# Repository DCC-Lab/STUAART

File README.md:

# STUAART

Repository of the STUAART project. 
Authors of this README : Valérie Pineau Noël, Nathan Bérubé and Daniel C. Côté (DCC/M-lab, CERVO brain research center, Université Laval)

## Overview

STUAART is an automated weighing system for mice that tracks individual weights over weeks. Each cage holds three independent scales ; each scale is a load cell (Wheatstone bridge) read by an HX711 24-bit amplifier connected via a 2-pin protocol (DOUT, SCK) to a DFRobot FireBeetle ESP32 V1 microcontroller. The microcontroller logs every measurement to a microSD card and exposes a small HTTP server so a host can pull today's CSV over Wi-Fi.

## Repository layout

| Folder | What's there |
|---|---|
| `Arduino/` | Custom libraries and scripts to run the STUAART. |
| `KiCAD/` | PCB schematic and design mde on KiCAD (version 10.0.7). |
| `CAD/` | Mechanical 3D files for the scale platforms. Print the top platform with high infill density to keep stiffness and reduce creep. |
| `FlaskServer/` | Python script used to catch the data and save on a local NAS. |
| `Notebooks/` | Notebooks that users can run in Google Colaboratory for data post-processing. |

## Getting started with the firmware

1. Install Arduino IDE 2.x or `arduino-cli`.
2. Add the Espressif boards URL in Preferences and install the `esp32` core (board package). 
3. Copy and save files in folder `Arduino` on your computer. 
4. Copy and save the Python script in `FlaskServer` in your local NAS and run it. 
5. If you are using a new Firebeetle ESP-32 board, run `Arduino/FormatSPIFFS/FormatSPIFFS.ino` (prevent error `SPIFFS Mount Failed`). Otherwise, go to the next step. 
6. Open `Arduino/STUAART/STUAART.ino`.
7. Download third-party libraries in the Arduino IDE. See section *Required third-party libraries*.
8. In the Arduino IDE, pick board `FireBeetle-ESP32` (`esp32:esp32:firebeetle32`) in  Tools -> Port, pick the USB serial port, then Verify and Upload.

## Required third-party libraries

Install these via Arduino IDE Library Manager (Sketch -> Include Library -> Manage Libraries):

| Library | Author | Tested version |
|---|---|---|
| HX711 | Bogdan Necula (bogde) | 0.7.5 |
| RTClib | Adafruit | 2.1.4 |
| ArduinoJson | Benoit Blanchon | 7.0.4 |

## A minimal load cell read

```cpp
#include "LoadCell.h"
#include "LoadCellController.h"

LoadCell loadcell;
LoadCellController controller;

void setup() {
  Serial.begin(115200);
  controller.add_loadcell(loadcell);
  controller.easy_start_with_params(
      1,        // loadcell number
      27,       // DOUT pin (avoid GPIO 6-11, those are the flash bus)
      17,       // SCK pin
      true,     // calibrate offset
      true,     // calibrate scale
      false,    // read offset from memory
      false,    // read scale from memory
      true,     // save offset to memory
      true,     // save scale to memory
      0,        // manual tare offset (0 = not specified)
      0,        // manual scale coeff (0 = not specified)
      128       // gain, do not change
  );
}

void loop() {
  controller.wait_ready_timeout(1, 1000);
  float reading = controller.get_weight(1);
  Serial.println(reading);
}
```

## Manual calibration mode VS Automatic mode

STUAART has a switch that dictates the mode at reboot. Manual calibration mode is used to save new persistent parameters (tare offset and scale coefficients) in the SPIFFS. These parameters are used to convert digital signals received from the HX711 amplifier to mass values in grams. For this step, objects of known mass must be used. The users can use as many objects of known mass as they want for calibration. Automatic mode is used when the users want to use the parameters previously saved in the SPIFFS. The authors suggest to start with the manual calibration mode when starting a new experiment. Connecting the STUAART to a computer will allow the users to make sure that everything is working well and save new calibration parameters. Then, for continuous, longitudinal measurements, the automatic mode can be turned on and the system can be powered via a standard wall adaptor. 

## Mass time series analysis

Each step of the post-processing analysis can be performed using notebooks run via Google Colaboratory. To begin, the raw mass time series must be uploaded to the user's personal Google Drive. We also recommend that users save a personal copy of each notebook to their own Google Drive by clicking on *File > Save a copy in Drive* once opened via the links below. Users are free to modify their own versions of the notebooks as desired. 

1. **Remove buffer flush indicators from the raw mass time series** : String such as "--, --, --, -- \n" are saved in the raw data to indicate the moments when the buffer flushed its contents onto the SD card. This data can be used to evaluate the time it takes to flush all data and how many times the buffer flushes the data over a given period. For further analysis, these indicators nust be removed. You can do this using this notebook :

2. **Correct for baseline shift and remove outliers** : This step is the most computationally intensive. Longitudinal mass time series are affected by mechanical and thermal drifts that alter the value of the initial tare and shift the measured mass by multiple grams, which must be corrected to ensure accuracte evaluation. Additionally, transient spikes can occur and should be filtered out. Users can choose whether to remove outliers and select which baseline correction algorithm best suits their data. Four baseline correction algorithms are provided : density-based spatial clustering of applications with noise (DBSCAN), kernel-density estimation (KDE), Gaussian mixture model (GMM) and a custom rolling-mean filtering. As presented in the main manuscript, the authors achieved optimal results with DBSCAN, while the custom rolling-mean filtering performs well for more stable data sets. We also provide a graphical user interface (GUI) for manual baseline fine-tuning and quick data visualization. We suggest testing different algorithms and using the notebook *Compute_metrics.ipnyb* to evaluate quantitatively the accuracy and precision of the baseline-corrected mass compared to ground-truth mass measurements. If ground-truth data was not acquired, a simple visual inspection of the baseline-corrected mass time series can guide algorithm selection. More information is available in the supplementary information document and within the notebook :

3. **Display mass time series and compute mass per time bin** : After baseline correction and outlier removal, the users can display the mass time series for visual evaluation. The data can be displayed per scale, for the overall measured mass of the system (summed mass time series per timepoint) and by the relative mass change (where the mass at time = 0 hour is 0%). The users can also obtain the mass per time bin. 

4. **Compute metrics** : Quantitative evaluation of the mass compared to ground-truth measurements can be obtained via this notebook : 

5. **Evaluate location, grid-hanging and active state behaviors** : Three additional notebooks are provided to identify and evaluate the spatial occupancy of each scale, the grid-hanging behavior and the active VS inactive states over time. 
   - Location : 
   - Hanging : 
   - Activity : 

## Error management 

- `Unable to verify flash chip connection` : the default upload speed of 921600 baud is too fast for the CH340 USB-serial chip on the FireBeetle. Set 115200. 

- `SPIFFS Mount Failed` : Run the script in `Arduino/FormatSPIFFS/FormatSPIFFS.ino`. 

- The "GPIO 9 = flash" issue on cell 1 is the root cause of corrupted readings (raw == 0xFFFFFF returned as -160.68 g). A defensive software patch in `LoadCell.cpp` rejects this signature, but the long-term fix is to reroute that DOUT to GPIO 25 or 26 (silkscreen D2 or D3).

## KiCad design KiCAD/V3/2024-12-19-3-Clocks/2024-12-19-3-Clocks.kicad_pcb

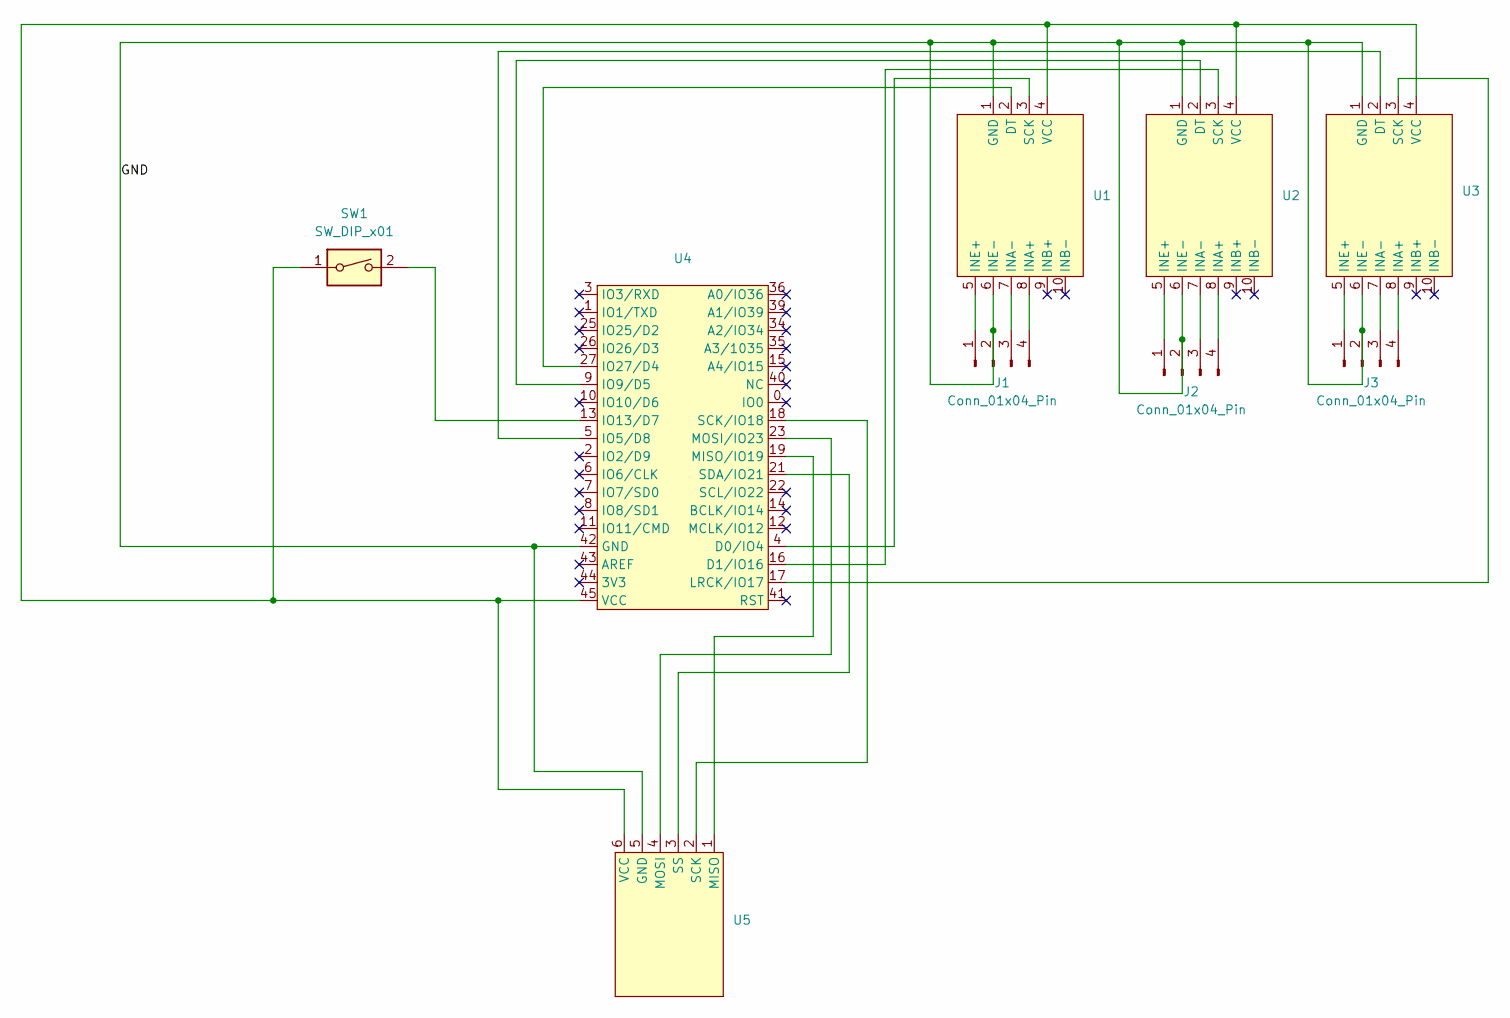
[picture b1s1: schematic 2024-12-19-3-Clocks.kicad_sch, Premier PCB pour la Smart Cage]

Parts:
J1, J2, J3: Conn_01x04_Pin; JST_PH_B4B-PH-K_1x04_P2.00mm_Vertical
SW1: SW_DIP_x01; SWITCH SLIDE DIP SPST 25MA 24V
U1, U2, U3: HX711
U4: Firebeetle ESP32
U5: MicroSD DFRobot

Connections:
/GND: J1.2, J2.2, J3.2, U1.1 (GND), U1.6 (INE-), U2.1 (GND), U2.6 (INE-), U3.1 (GND), U3.6 (INE-), U4.42 (GND), U5.5 (GND)
unnamed: J1.1, U1.5 (INE+)
unnamed: J1.3, U1.7 (INA-)
unnamed: J1.4, U1.8 (INA+)
unnamed: J2.1, U2.5 (INE+)
unnamed: J2.3, U2.7 (INA-)
unnamed: J2.4, U2.8 (INA+)
unnamed: J3.1, U3.5 (INE+)
unnamed: J3.3, U3.7 (INA-)
unnamed: J3.4, U3.8 (INA+)
unnamed: U1.2 (DT), U4.27 (IO27/D4)
unnamed: U1.3 (SCK), U4.4 (D0/IO4)
unnamed: SW1.1, U1.4 (VCC), U2.4 (VCC), U3.4 (VCC), U4.45 (VCC), U5.6 (VCC)
unnamed: U2.2 (DT), U4.9 (IO9/D5)
unnamed: U2.3 (SCK), U4.16 (D1/IO16)
unnamed: U3.2 (DT), U4.5 (IO5/D8)
unnamed: U3.3 (SCK), U4.17 (LRCK/IO17)
unnamed: SW1.2, U4.13 (IO13/D7)
unnamed: U4.19 (MISO/IO19), U5.1 (MISO)
unnamed: U4.23 (MOSI/IO23), U5.4 (MOSI)
unnamed: U4.18 (SCK/IO18), U5.2 (SCK)
unnamed: U4.21 (SDA/IO21), U5.3 (SS)

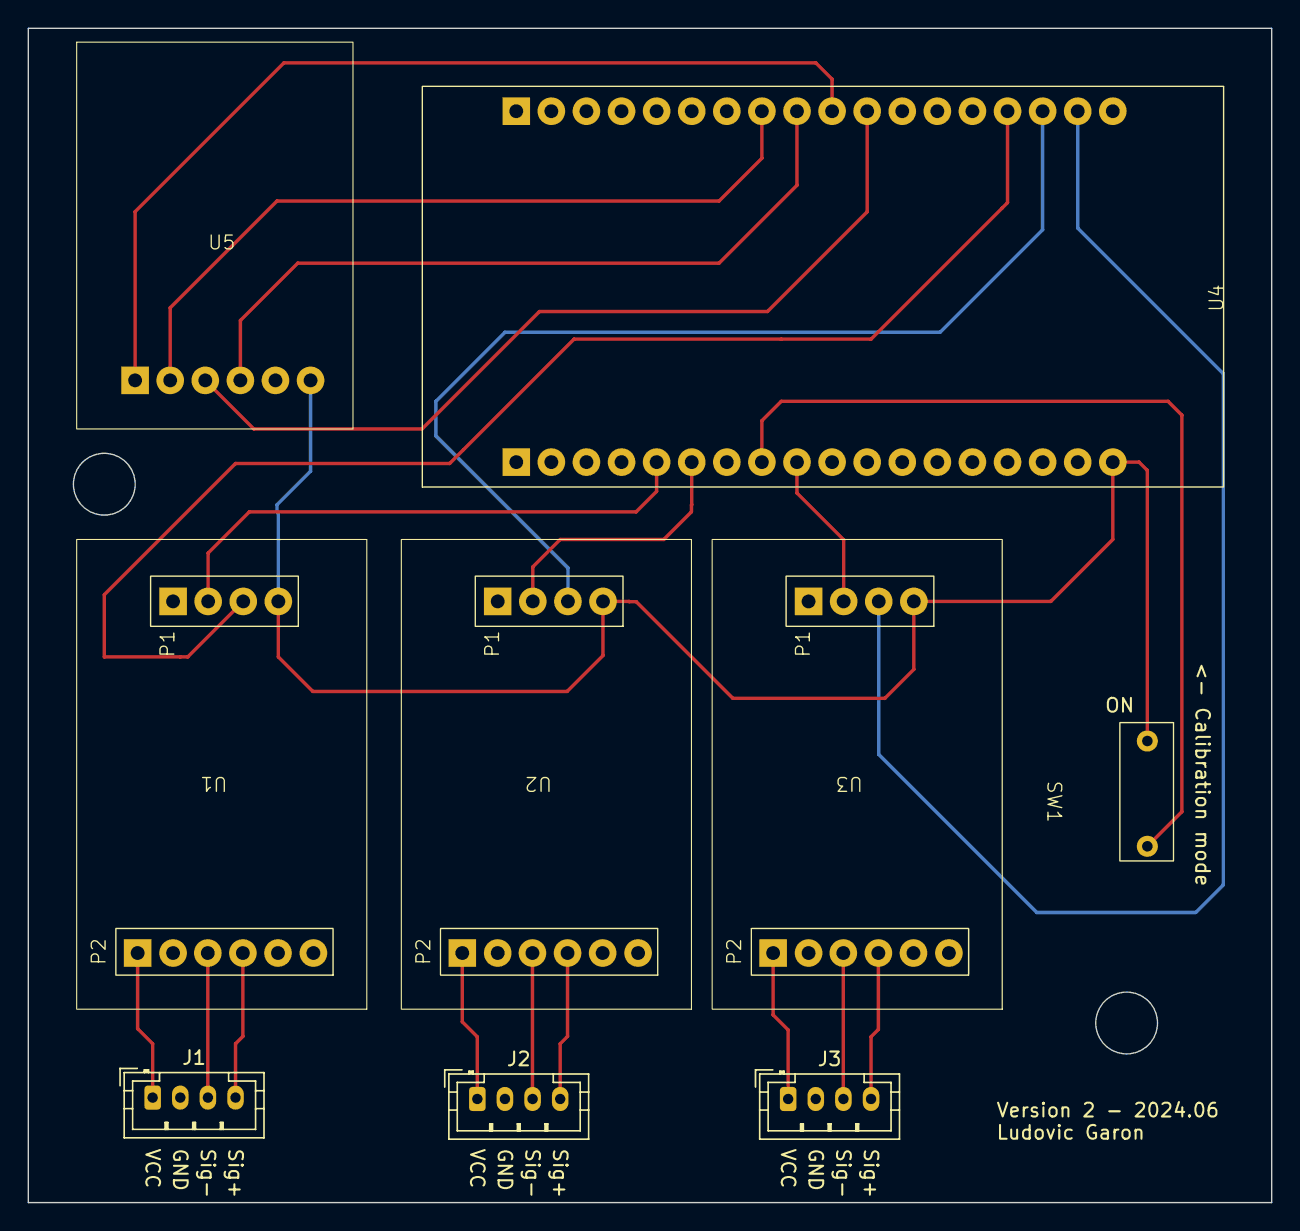
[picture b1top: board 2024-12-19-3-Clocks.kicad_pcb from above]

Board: 2 copper layers, 90.0 x 85.0 mm, 9 parts (0 on the bottom side), 22 nets.

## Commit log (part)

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2023-07-13 Add drift data and drift arduino code
    Add drift data and drift arduino code used in all drift tests
2023-07-17 Change in files organisation
2023-07-18 Loadcell and Loadcell_controller librarieslibraries
    First commit of the two Arduino libraries
2023-07-19 Applying F() macro on strings/syntax corrections
    To avoid stocking strings in variables memory, the F() can be used to save on sketch memory. The variables was full without this step when compiling.
2023-07-19 Description of Loadcell_controller methods/make methods protected
    Easy_ methods were put in protected since they are only called in easy_start_with_params() and calling them somewhere else wouldn't be adapted.
2023-08-16 Add doxygen documentation and comment
    The two libraries were documented with doxygen formated docstrings. A few functions were added to LoadCellController class to access a LoadCell completely through the LoadCellController
2023-08-16 Add link to github for libraries in headings
2023-08-18 Modification CAD .stl files
2023-08-20 change in folde name
2023-08-20 File name change
2023-08-21 Add capacitive sensor sketch example
2023-08-22 Change directory name
2023-09-26 Update README.md with an easy start code for one loadcell
2023-10-11 LoadCellController compiles for EEPROM and SPIFFS
    The read/save_from_peristent_memory now support both EEPROM and SPIFFS. The code detects wich chip is connected and the behaviour of the member functions are adapted to the type of memory. Not tested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
2023-11-01 SPIFFS fully working
    The library is now adapted to support both EEPROM and SPIFFS. The documentation was adapted to this new version.
2023-11-02 Sketch to format SPIFFS
    Creation of a sketch to format SPIFFS on a FireBeetle when used for the first time
2023-11-10 Update WeightReadingWithRecalibrationModeSwitching.ino
    Remove useless Serial.print()
2023-11-24 Add sketch examples
    Modify the mode switching sketch to make it work with SD card. Adding a file with functions which can manage the file on the SD card and read them.
2023-12-10 Linear test
    Adding the data, python code for graph and the firebeetle sketch for the linearity test of a 100g load cell.
2023-12-20 Test of a 300g load cell with 200g
    Arduino sketch for the experiment, the csv data file and the python code to produce a simple graph.
2024-01-12 Create TestLoadCellandHX711.ino
    Creation of a simple script to verify if all components are working
2024-01-12 Create LoadCellCircuit.png
    Scheme of the circuit for a load cell
2024-02-07 Correct number of readings averaged bug
    The read_average() from HX711 library was used instead of read_raw_average(). No number of averaged readings was specified in input because my custom library always uses the class variable. But, read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
2024-02-14 Recalibration of offset with absolute value on measurement
    The condition of recalibration if the offset in get_weight_with_auto_recalibration() is a threshold. The comparison between the measurement and the threshold wasn't unsigned. The absolute value is no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
2024-02-14 Create 20240214_outliersfiltering.py
    First version of outliers filtering on weight data with python
2024-03-20 Add new raw weight data with mouse (2024.02.14)
2024-03-20 Add super().__init__ in Data class
    make sure that the Data object will have all the attributes of np.ndarray type
2024-03-27 Add all visualization functions and simple filtering
2024-04-03 Baseline fitting version 1
    First version of the baseline fitting functions.
2024-04-10 Référer à mon .md pour les petits changements que j'ai faits
2024-04-16 2024.04.15 : Ajout d'un seuil pour les outliers négatifs qui est différent du seuil pour les outliers positifs
2024-04-17 Update and add docstring shift_data_to_zero function
    I changed the name center_data_on_zero to shift_data_on_zero to make it clear that the data is only shifted to zero and not around its mean
2024-04-17 Complete documentation of functions in Data class
2024-04-17 Add documentation and correct a few mistakes
2024-05-07 creating 2 main.py version
    mainv2.py uses the Cage class
2024-05-07 add fft filtering
2024-05-07 add automatic initial offset calculation
    first offset is now calculated from the first stable values. average is taken. the code can find how many values to average based on a tolerance on stability
2024-05-07 update mainv1.py for tests
    commenting and uncommenting sections to see signal at different steps in processing
2024-05-21 Adding convolution filtering
2024-05-21 add comments in mainv2
2024-05-28 indent fix
2024-05-28 Added files based on 2023-11-27 code
2024-05-29 Added creation of test files and changed wifi name/password
2024-05-29 Moved file to fit arduino, Changed way we send data
2024-05-30 Put every functions before arduino setup and loop
2024-05-30 Started documentation, put the saved files in a folder in user documents
2024-05-30 Added doc to python methods
2024-05-30 Added functions documentation in the arduino code
2024-05-30 added log folder to keep things clean
2024-05-30 Smooth mean weight change over time and correct for boundary effects from convolution
    - convolution_filter() is now convolution)filter_with_egde_padding(). The boundary effect from the convolution filtering is corrected with edge padding.
    - added the function "reset_data()" to reset the data to the raw data after a certain task is completed.
    - the function compute_mean_data() produces a smooth weight change over time. The level of smoothness can be adapted with the variable smooth_level.
    -
2024-05-31 added mechanism to create a file everyday to which we should concatenate.
    Added a small part of code to make it minutes rather than days because otherwise it would be too long to test easily.
2024-05-31 Added first delayed fetch of the data
2024-05-31 Standardized the naming conventions
2024-05-31 Added a function to generate a number of ips from the first one and the number of ips that you want
2024-06-03 renamed and now using non-deprecated accessors
2024-06-03 Add Cage Sketch to measure weight (used on 20240407)
2024-06-03 fixed function description to fit actual function
2024-06-03 Copied files from 20240530 to continue
2024-06-04 Fixed writing to files so we create rows with each data
2024-06-04 Moved folders to make it more manageable and to keep traceability.
    We should always modify the same file rather than creating new ones for every test.
2024-06-05 reindented code
2024-06-05 commented out code and made it save every day
2024-06-06 Total hanging is done
    I made the total hanging time accuracy and the hanging identification accuracy. I changed the way we remove outliers, I added a function in CageClass to identify when the mouse gets in the cage at th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
2024-06-06 added security to make sure we don't save today's data in tomorrow's file. Shouldn't happen, but better be safe than sorry
2024-06-06 added reconnection to wifi after an hour to make sure the device stays connected. Commented out most of the serial prints to get faster acquisition
2024-06-07 server accepts a custom file specified to be sent
2024-06-07 added test file and buffering data
2024-06-07 accelerated data transfer over wifi
2024-06-07 made delays between failed attempts to download an hour rather than 30 seconds to give the Firebeetle time to reconnect.
2024-06-10 added function comments on saving to server
2024-06-10 testing thread timer
2024-06-10 removed test csv
2024-06-11 changed from 6 hours loops to 12 hours
2024-06-13 Hanging moments are identified with a total time accuracy of 88.6% and a hanging identification accuracy of 90.9%
    Hanging is identified by :
    - removing outliers, aka removing measurements that are alone and very different from its neighbours.
    - convoluting with a small window (15 points) and doing the mean, so passing a square function
    - using the function compute_hanging(), which identifies the total hanging time, the moment of hanging and the hanging frequency.
    I compare my results with the real moments of hanging that I identified manually from the video.
2024-06-13 Hanging events are identified correctly
    1. Remove outliers (outliers = points that are very different from their neighbours)
    2. Convolve with a small window (15 points) to smoothen the data
    3. High-pass filter in convolution. Identifies moments when the weight data changes drastically.
    4. I use conditions to verify where are the hanging events according to the number of points between the start index and the end index. For example, if the number of points between start and end is u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
2024-06-13 Done
2024-06-22 Small corrections + test new measurements from pcb version 2
2024-06-27 put the saving interval to 0
2024-06-27 creating folders on remote server recursively
2024-07-02 modified comment to make it clearer
2024-07-02 Added calendar ui with button sending the file we want to fetch
2024-07-04 added build files to gitignore
2024-07-04 added method documentation
2024-09-03 Paste last script for overnight mouse recording
2024-09-03 Added kicad files for pcb v2
2024-09-18 Update CageClass.py
    je regarde maintenant tous les pics ensemble, sans discriminer les négatifs et les positifs, suite à un filtre passe-haut sur les séries temporelles de poids et je regarde tous les intervalles si la 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
    Ça fonctionne super bien SEULEMENT quand la souris est sur une balance à la fois
2024-09-26 Compute number of entries per scale
    compute_location_on_scale() will now compute the number of entries per scale.
2024-10-10 Location is identified and evaluated compared to ground truth from video
    The location of the mouse is identified correctly with the weight data from individual time series of each scale. The total error and precision is computed as well with a different class method.
2024-12-04 Added forced fast clock and SD card library
2024-12-18 Moved load cell library files inside arduino folder so when we modify the code it automatically modifies what is used
2024-12-18 added option to enable or disable save to SD Card taring of loadcells
2024-12-18 testing saving data with 3 loadcells
2024-12-18 PCA of dataset of 2 seconds per behaviour event is done and cluster somehow good the different data, but mostly the different scales
2024-12-19 This setup doesnt give outliers
2024-12-19 FFT of weight data
    FFT of weight data per type of behaviour is performed. There is no specific frequency that is present in the grooming that that can differentiate it from the other types of behaviour.
2024-12-19 Using different clock pins for the load cells
2024-12-19 Updated README.md, added small tutorial on how to use the branch
2025-02-17 Je ne sais pas
2025-03-31 Create Test2LoadCellandHX771.ino
    Sketch example to use two loadcells using two different sck pins and only reading raw data.
2025-03-31 Update Test2LoadCellandHX771.ino
    change description in the sketch
2025-05-28 IMproved the README for completeness
    Added more context
    Added table of content
    Added info on exact versions of libraries to install
    Added info on where to find the library directory
2025-05-28 Update FireBeetleServer.ino
    IMproved use of logf() through out the main code.
2025-06-03 Many changes, mostly cosmetics, but some imnportant
    * The LoadCell and LoadCellController are now in the main directory of the ino file.
    They do not need to be in the librairies folder, and this makes verything simpler
    since they remain in the Git context.
    * Now using the ArduinoLog libraries for a clean, controllable log with log_levels.
    * Reformatted everything
2025-06-04 IMproved time kleeping: fall back on time since boot if date is not available.
    Also, use string instead of char*;
2025-10-01 Remove comment in 20250924-SketchExampleOneScaleSDCardSwitchWifi.ino
2025-10-01 Add network and password information to 20250924-SketchExampleOneScaleSDCardSwitchWifi.ino
2025-10-27 Change threshold to find peaks from 15 to 10 to identify correctly hanging events
2025-11-03 Print baseline data and its FFT of the system and of the 3 scales separately
2025-11-04 PCA and ICA on power spectra, then HDBSCAN
    Both don't really work, but PCA with the power spectra are somewhat promising.
2025-12-09 Test identifying grooming-like behaviour
2025-12-09 I am computing 4 features on 2 sec time windows with a step size of 1 sec
2026-02-27 Modify fetch_data() and fetch_date() to simplify the request
2026-03-02 file_fetcher_2.py IS DONE
    STUAART Data Fetcher
    Overview
    This Python application is a central component of the STUAART (Smart Cage System), designed for automated longitudinal monitoring in biophotonics and neuroscience research (specifically for ABA mouse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
    The script automates the retrieval of high-density mass time-series data from multiple IoT-enabled mouse cages (FireBeetle ESP32) and manages the multi-stage archival process from the laboratory to r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
    Key Features
    1. Multi-Stage Data Pipeline
